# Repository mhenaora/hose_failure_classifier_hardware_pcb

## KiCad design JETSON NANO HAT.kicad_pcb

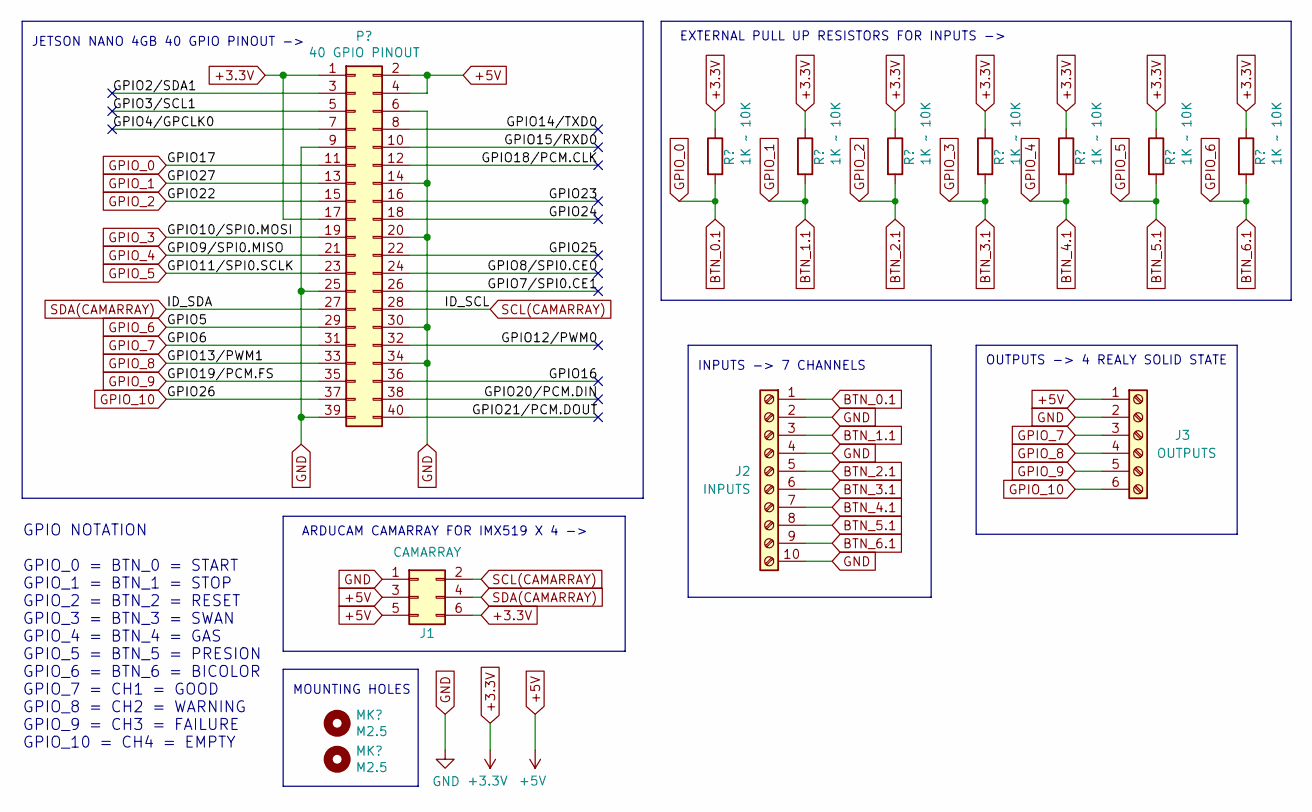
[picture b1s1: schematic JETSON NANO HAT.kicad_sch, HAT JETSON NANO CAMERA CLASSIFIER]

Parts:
J1: CAMARRAY; PinHeader_2x03_P2.54mm_Vertical
J2: INPUTS; TerminalBlock_Phoenix_PT-1,5-10-3.5-H_1x10_P3.50mm_Horizont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
J3: OUTPUTS; TerminalBlock_Phoenix_PT-1,5-6-3.5-H_1x06_P3.50mm_Horizontal
MK1, MK2: M2.5; MountingHole_2.7mm_M2.5
P1: 40 GPIO PINOUT; PinSocket_2x20_P2.54mm_Vertical
R1, R2, R3, R4, R5, R6, R7: 1K ~ 10K; R_1206_3216Metric

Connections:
+3.3V: J1.6, P1.1, P1.17, R1.1, R2.1, R3.1, R4.1, R5.1, R6.1, R7.1
+5V: J1.3, J1.5, J3.1, P1.2, P1.4
/GPIO2/SDA1: P1.3
/GPIO3/SCL1: P1.5
/GPIO4/GPCLK0: P1.7
/GPIO7/SPI0.CE1: P1.26
/GPIO8/SPI0.CE0: P1.24
/GPIO12/PWM0: P1.32
/GPIO14/TXD0: P1.8
/GPIO15/RXD0: P1.10
/GPIO16: P1.36
/GPIO18/PCM.CLK: P1.12
/GPIO20/PCM.DIN: P1.38
/GPIO21/PCM.DOUT: P1.40
/GPIO23: P1.16
/GPIO24: P1.18
/GPIO25: P1.22
BTN_0.1: J2.1, P1.11, R1.2
BTN_1.1: J2.3, P1.13, R2.2
BTN_2.1: J2.5, P1.15, R3.2
BTN_3.1: J2.6, P1.19, R4.2
BTN_4.1: J2.7, P1.21, R5.2
BTN_5.1: J2.8, P1.23, R6.2
BTN_6.1: J2.9, P1.29, R7.2
GND: J1.1, J2.2, J2.4, J2.10, J3.2, P1.6, P1.9, P1.14, P1.20, P1.25, P1.30, P1.34, P1.39
GPIO_7: J3.3, P1.31
GPIO_8: J3.4, P1.33
GPIO_9: J3.5, P1.35
GPIO_10: J3.6, P1.37
SCL(CAMARRAY): J1.2, P1.28
SDA(CAMARRAY): J1.4, P1.27

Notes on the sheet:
JETSON NANO 4GB 40 GPIO PINOUT ->
MOUNTING HOLES
INPUTS -> 7 CHANNELS
OUTPUTS -> 4 REALY SOLID STATE
ARDUCAM CAMARRAY FOR IMX519 X 4 ->
GPIO NOTATION GPIO_0 = BTN_0 = START GPIO_1 = BTN_1 = STOP GPIO_2 = BTN_2 = RESET GPIO_3 = BTN_3 = SWAN GPIO_4 = BTN_4 = GAS GPIO_5 = BTN_5 = PRESION GPIO_6 = BTN_6 = BICOLOR GPIO_7 = CH1 = GOOD GPIO_8 = CH2 = WARNING GPIO_9 = CH3 = FAILURE GPIO_10 = CH4 = EMPTY
EXTERNAL PULL UP RESISTORS FOR INPUTS ->

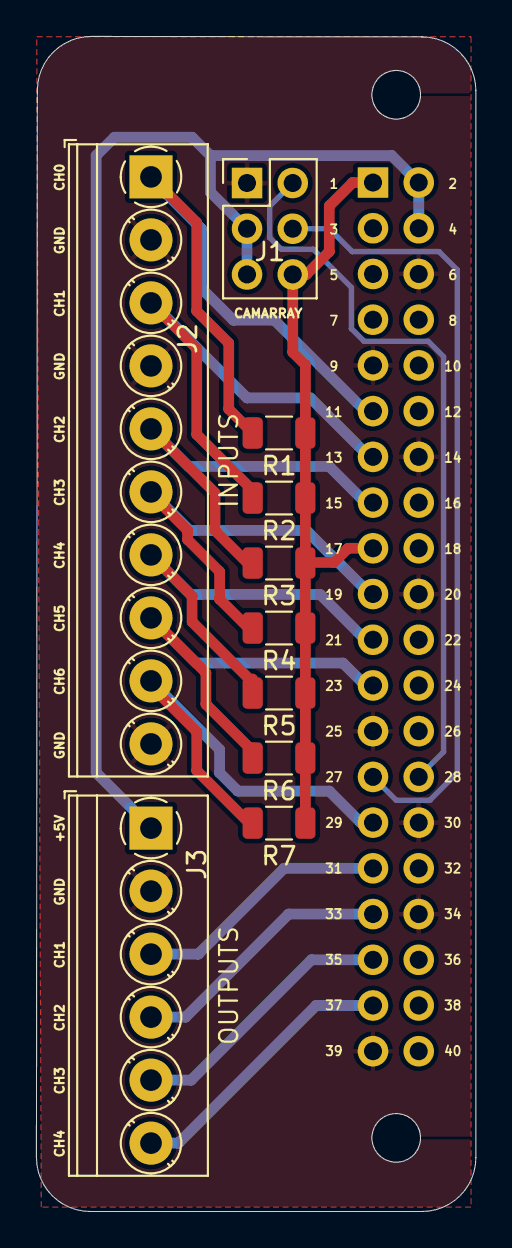
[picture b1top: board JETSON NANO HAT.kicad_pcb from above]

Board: 2 copper layers, 24.4 x 65.3 mm, 13 parts (1 on the bottom side), 16 nets.

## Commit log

2023-08-02 base version 6 inputs 4 outputs
2023-08-02 new input added : 7 inputs 4 outputs & .sch - .pcb updated
